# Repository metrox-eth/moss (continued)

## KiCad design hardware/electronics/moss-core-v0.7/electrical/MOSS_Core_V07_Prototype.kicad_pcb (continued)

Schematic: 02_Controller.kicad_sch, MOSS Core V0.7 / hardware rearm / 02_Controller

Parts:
C6: 10uF; Capacitor_SMD_C_0805_2012Metric; MPN GRM21BR71A106KA73L
C7, C41: 100nF; Capacitor_SMD_C_0603_1608Metric; MPN GRM188R71C104KA01D
D2: GREEN; LED_SMD_LED_0603_1608Metric; MPN LTST-C190KGKT
H1: M2.5 GND bond / drill2.7; MOSS_Mount_M2p5_GND_D8; MPN PCB_FEATURE
H2, H3, H4: M2.5 / drill 2.7 / keepout D8; MOSS_Mount_M2p5_2p7_D8; MPN NPTH
H5, H6, H7, H8: Orange Pi M2.5 / D6; MOSS_Mount_M2p5_2p7_D6; MPN NPTH
R5, R6: 10k; Resistor_SMD_R_0603_1608Metric; MPN RC0603FR-0710KL
R7: 1k; Resistor_SMD_R_0603_1608Metric; MPN RC0603FR-071KL
R8, R9: 4.7k; Resistor_SMD_R_0603_1608Metric; MPN RC0603FR-074K7L
SW1: RESET_N; Button_Switch_SMD_SW_Push_1P1T_NO_CK_KMR2; MPN KMR221NGLFS
SW2: BOOT_N; Button_Switch_SMD_SW_Push_1P1T_NO_CK_KMR2; MPN KMR221NGLFS
TP1: GND; TestPoint_TestPoint_Pad_D1.0mm; MPN PCB test pad
TP2: 3V3; TestPoint_TestPoint_Pad_D1.0mm; MPN PCB test pad
TP3: TX0; TestPoint_TestPoint_Pad_D1.0mm; MPN PCB test pad
TP5: SDA; TestPoint_TestPoint_Pad_D1.0mm; MPN PCB test pad
TP6: SCL; TestPoint_TestPoint_Pad_D1.0mm; MPN PCB test pad
TP7: RESET; TestPoint_TestPoint_Pad_D1.0mm; MPN PCB test pad
U1: ESP32-S3-WROOM-1U-N8; RF_Module_ESP32-S3-WROOM-1U; MPN ESP32-S3-WROOM-1U-N8
U20: TPS3808G33DBVR; Package_TO_SOT_SMD_SOT-23-6; MPN TPS3808G33DBVR

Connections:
3V3: C6.1, C7.1, C41.1, R5.1, R6.1, R8.1, R9.1, TP2.1, U1.2 (3V3), U20.5 (SENSE), U20.6 (VDD); also elsewhere on the board
ACT_POWER_ENABLE: U1.31 (IO38); also elsewhere on the board
ARM_COMMIT: U1.39 (IO1); also elsewhere on the board
ARM_LATCHED: U1.38 (IO2); also elsewhere on the board
AUDIO_BCLK: U1.18 (IO10); also elsewhere on the board
AUDIO_DATA: U1.20 (IO12); also elsewhere on the board
AUDIO_ENABLE: U1.21 (IO13); also elsewhere on the board
AUDIO_LRCLK: U1.19 (IO11); also elsewhere on the board
BOOT_N: R6.2, SW2.1 (A), U1.27 (IO0)
DEBUG_TX: TP3.1, U1.37 (IO43)
DIR_L: U1.10 (IO17); also elsewhere on the board
DIR_R: U1.12 (IO8); also elsewhere on the board
DRIVE_ENABLE: U1.23 (IO21); also elsewhere on the board
DRIVE_RUN: U1.36 (IO44); also elsewhere on the board
ENC_L_A: U1.7 (IO7); also elsewhere on the board
ENC_L_B: U1.6 (IO6); also elsewhere on the board
ENC_POWER_EN: U1.35 (IO42); also elsewhere on the board
ENC_R_A: U1.5 (IO5); also elsewhere on the board
ENC_R_B: U1.9 (IO16); also elsewhere on the board
ESP_USB_N: U1.13 (IO19); also elsewhere on the board
ESP_USB_P: U1.14 (IO20); also elsewhere on the board
ESTOP_ACTIVE: U1.4 (IO4); also elsewhere on the board
GND: C6.2, C7.2, C41.2, D2.1 (K), H1.1 (GND), SW1.2 (B), SW2.2 (B), TP1.1, U1.1 (GND), U1.40 (GND), U1.41 (GND), U20.2 (GND); also elsewhere on the board
I2C_SCL: R9.2, TP6.1, U1.33 (IO40); also elsewhere on the board
I2C_SDA: R8.2, TP5.1, U1.34 (IO41); also elsewhere on the board
LED_A: D2.2 (A), R7.2
PWM_L: U1.11 (IO18); also elsewhere on the board
PWM_R: U1.17 (IO9); also elsewhere on the board
RESET_N: R5.2, SW1.1 (A), TP7.1, U1.3 (EN), U20.1 (RESET_N); also elsewhere on the board
SERVO_RX: U1.30 (IO37); also elsewhere on the board
SERVO_TX: U1.28 (IO35); also elsewhere on the board
SERVO_TX_ENABLE: U1.29 (IO36); also elsewhere on the board
STATUS_LED: R7.1, U1.8 (IO15)
USB_PWR_FAULT_N: U1.22 (IO14); also elsewhere on the board
WD_ENABLE: U1.24 (IO47); also elsewhere on the board
WD_RESET_N: U20.3 (MR_N); also elsewhere on the board
WD_TICK: U1.25 (IO48); also elsewhere on the board

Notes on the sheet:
MOSS CORE V0.7 / ASYNC FAULT CLEAR + EXPLICIT REARM / 1 NOVEMBER 2026
GPIO1 ARM_COMMIT is a dedicated post-qualification pulse. GPIO2 reads ARM_LATCHED. Initial ACT_POWER_ENABLE remains independent of ACT_READY.

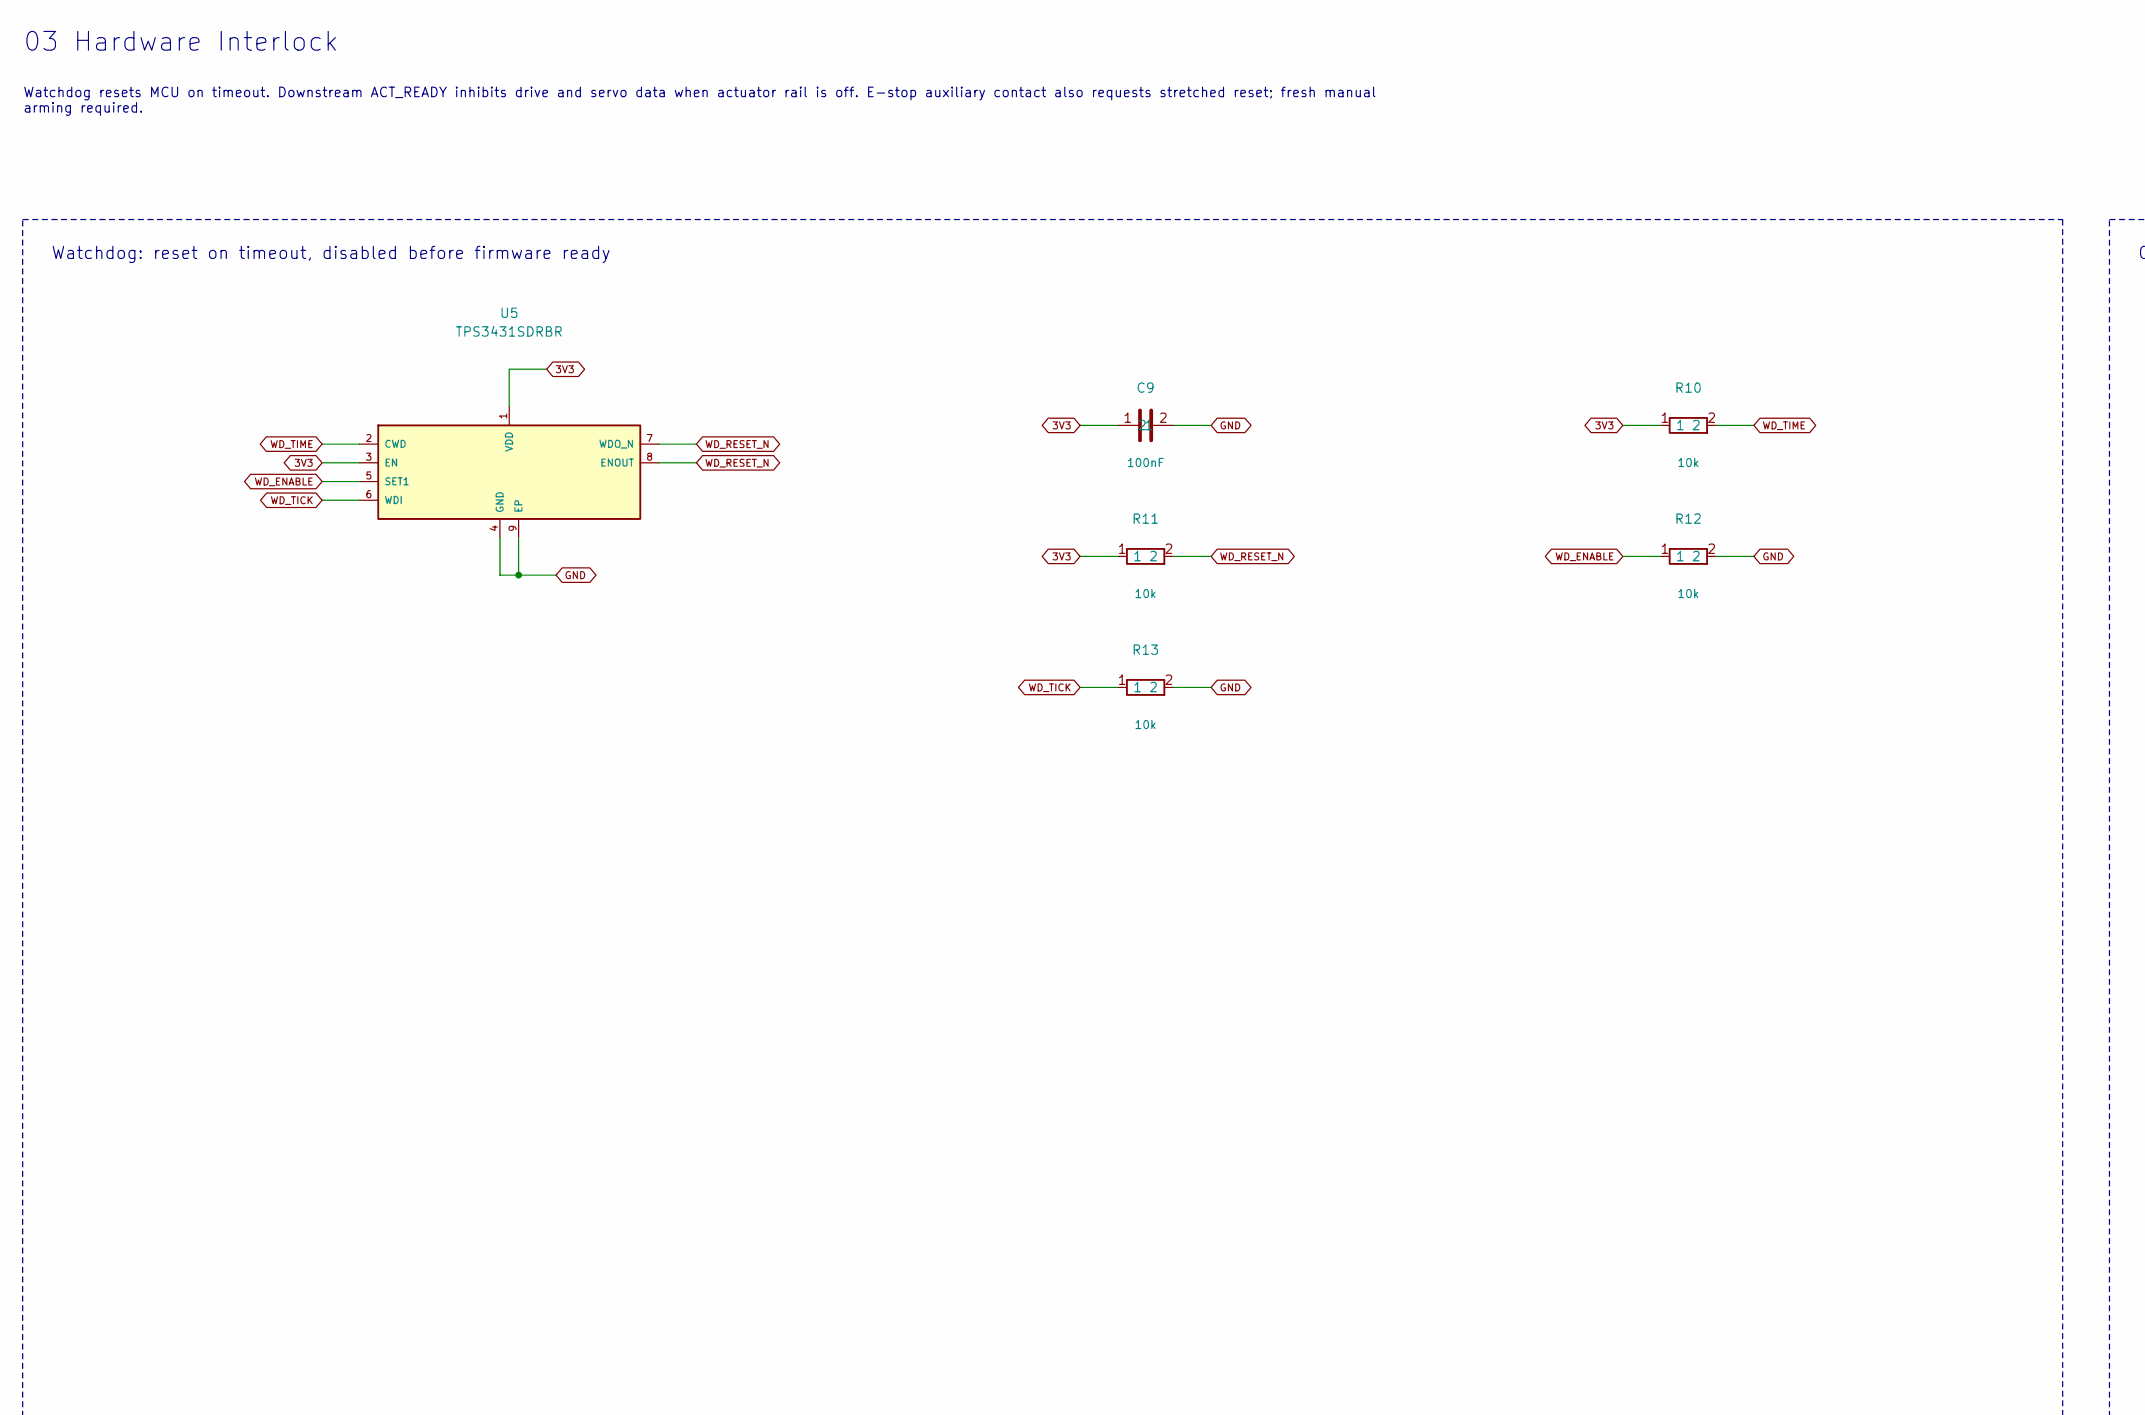
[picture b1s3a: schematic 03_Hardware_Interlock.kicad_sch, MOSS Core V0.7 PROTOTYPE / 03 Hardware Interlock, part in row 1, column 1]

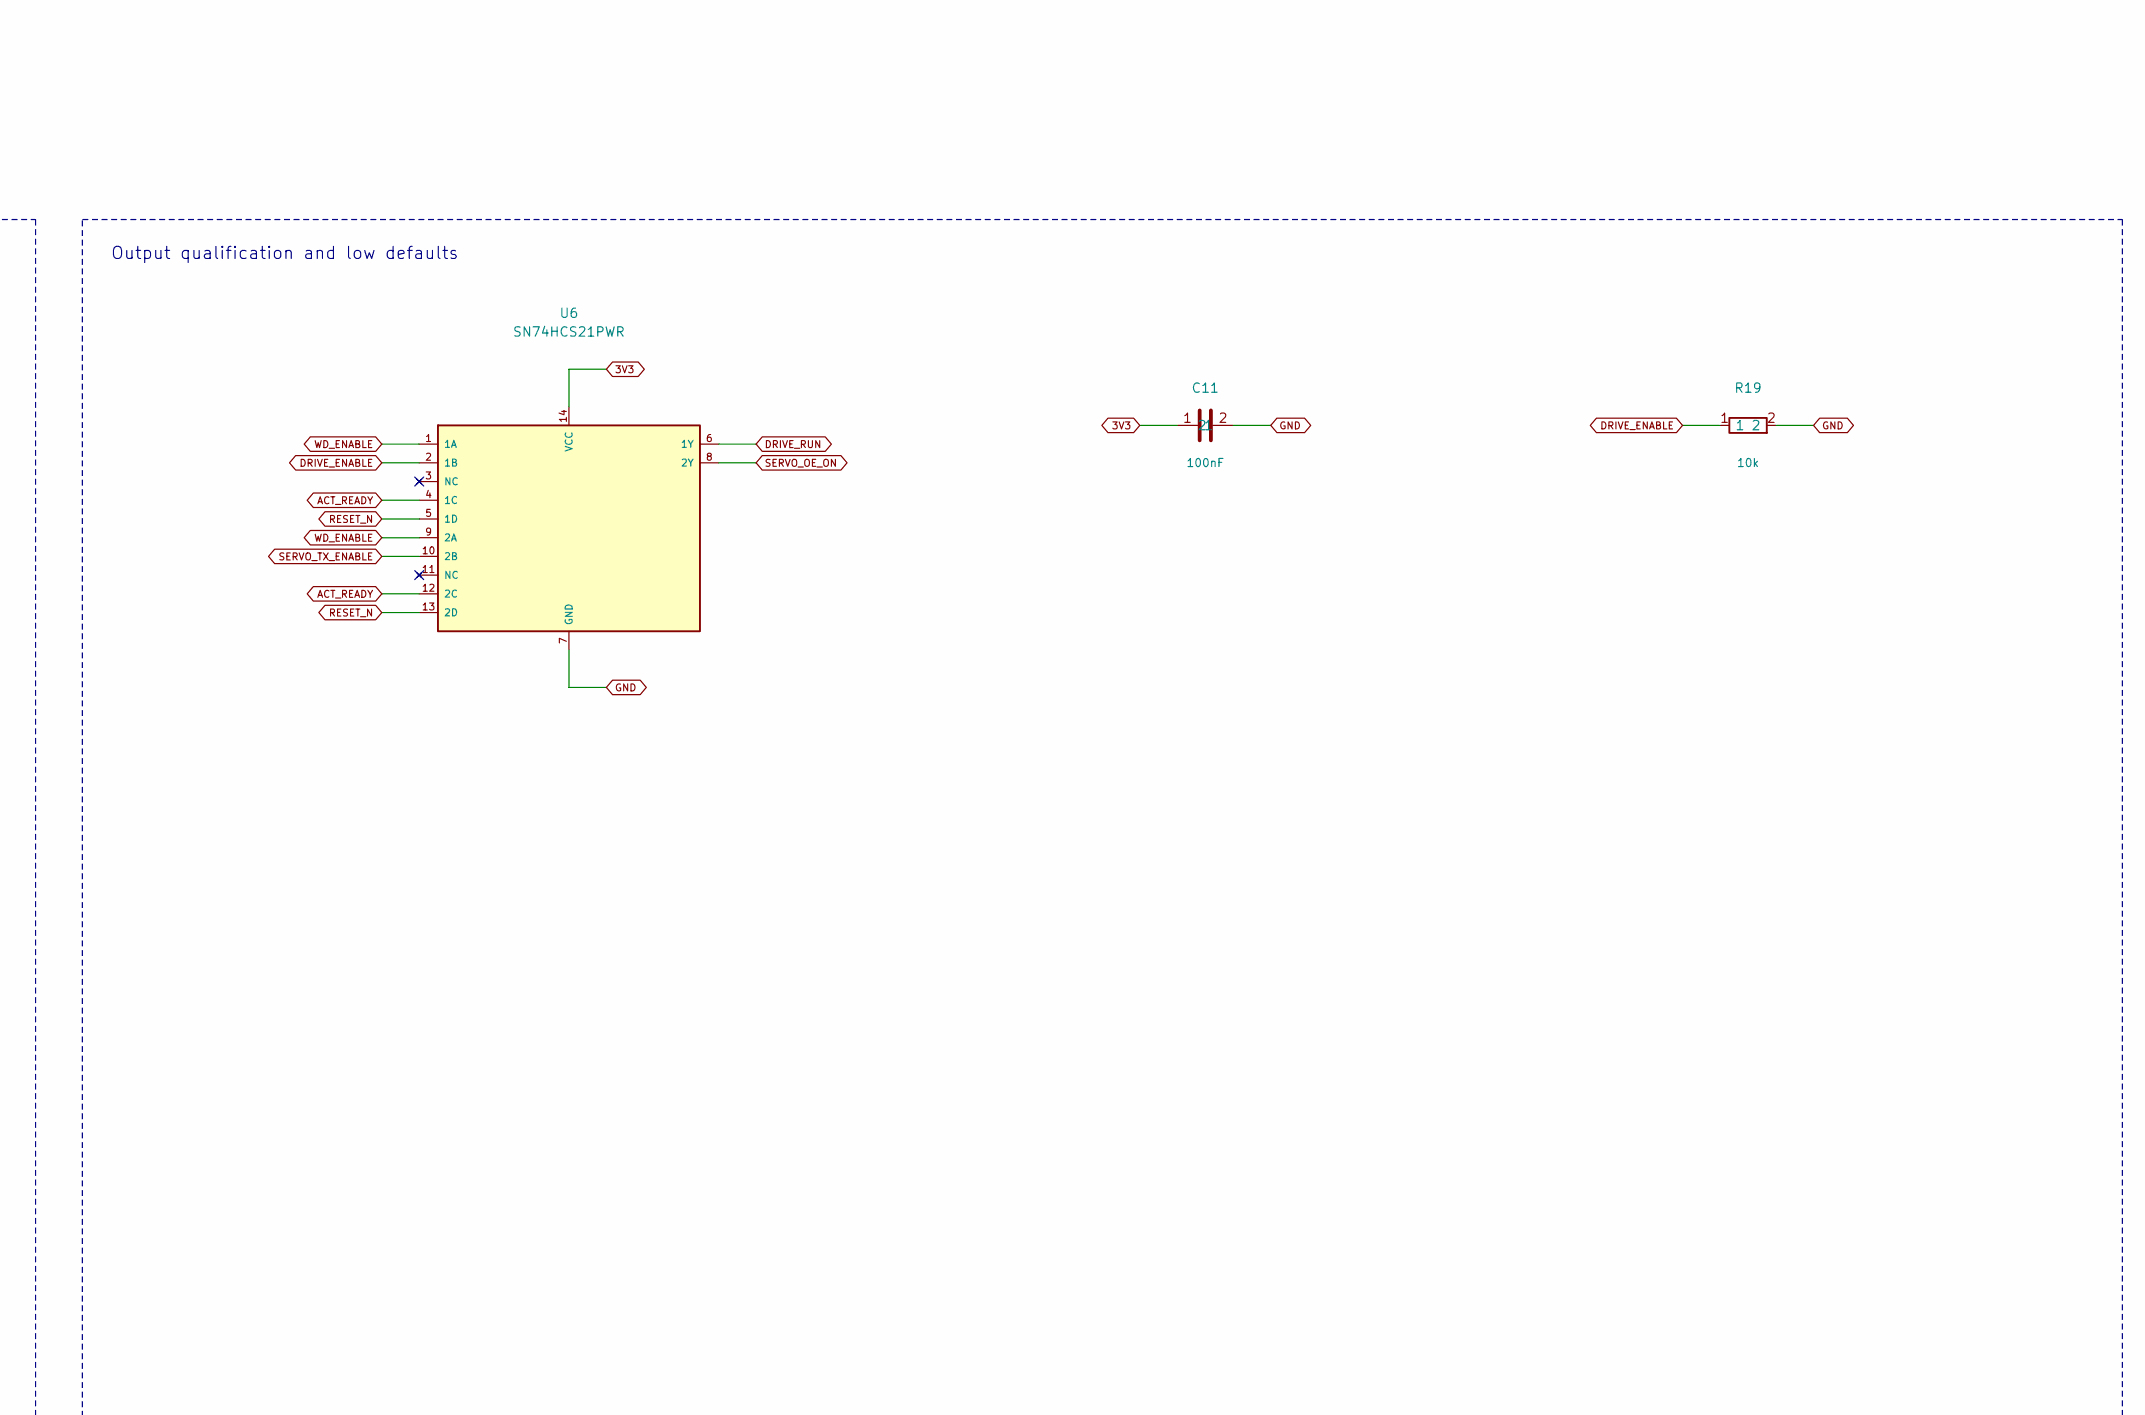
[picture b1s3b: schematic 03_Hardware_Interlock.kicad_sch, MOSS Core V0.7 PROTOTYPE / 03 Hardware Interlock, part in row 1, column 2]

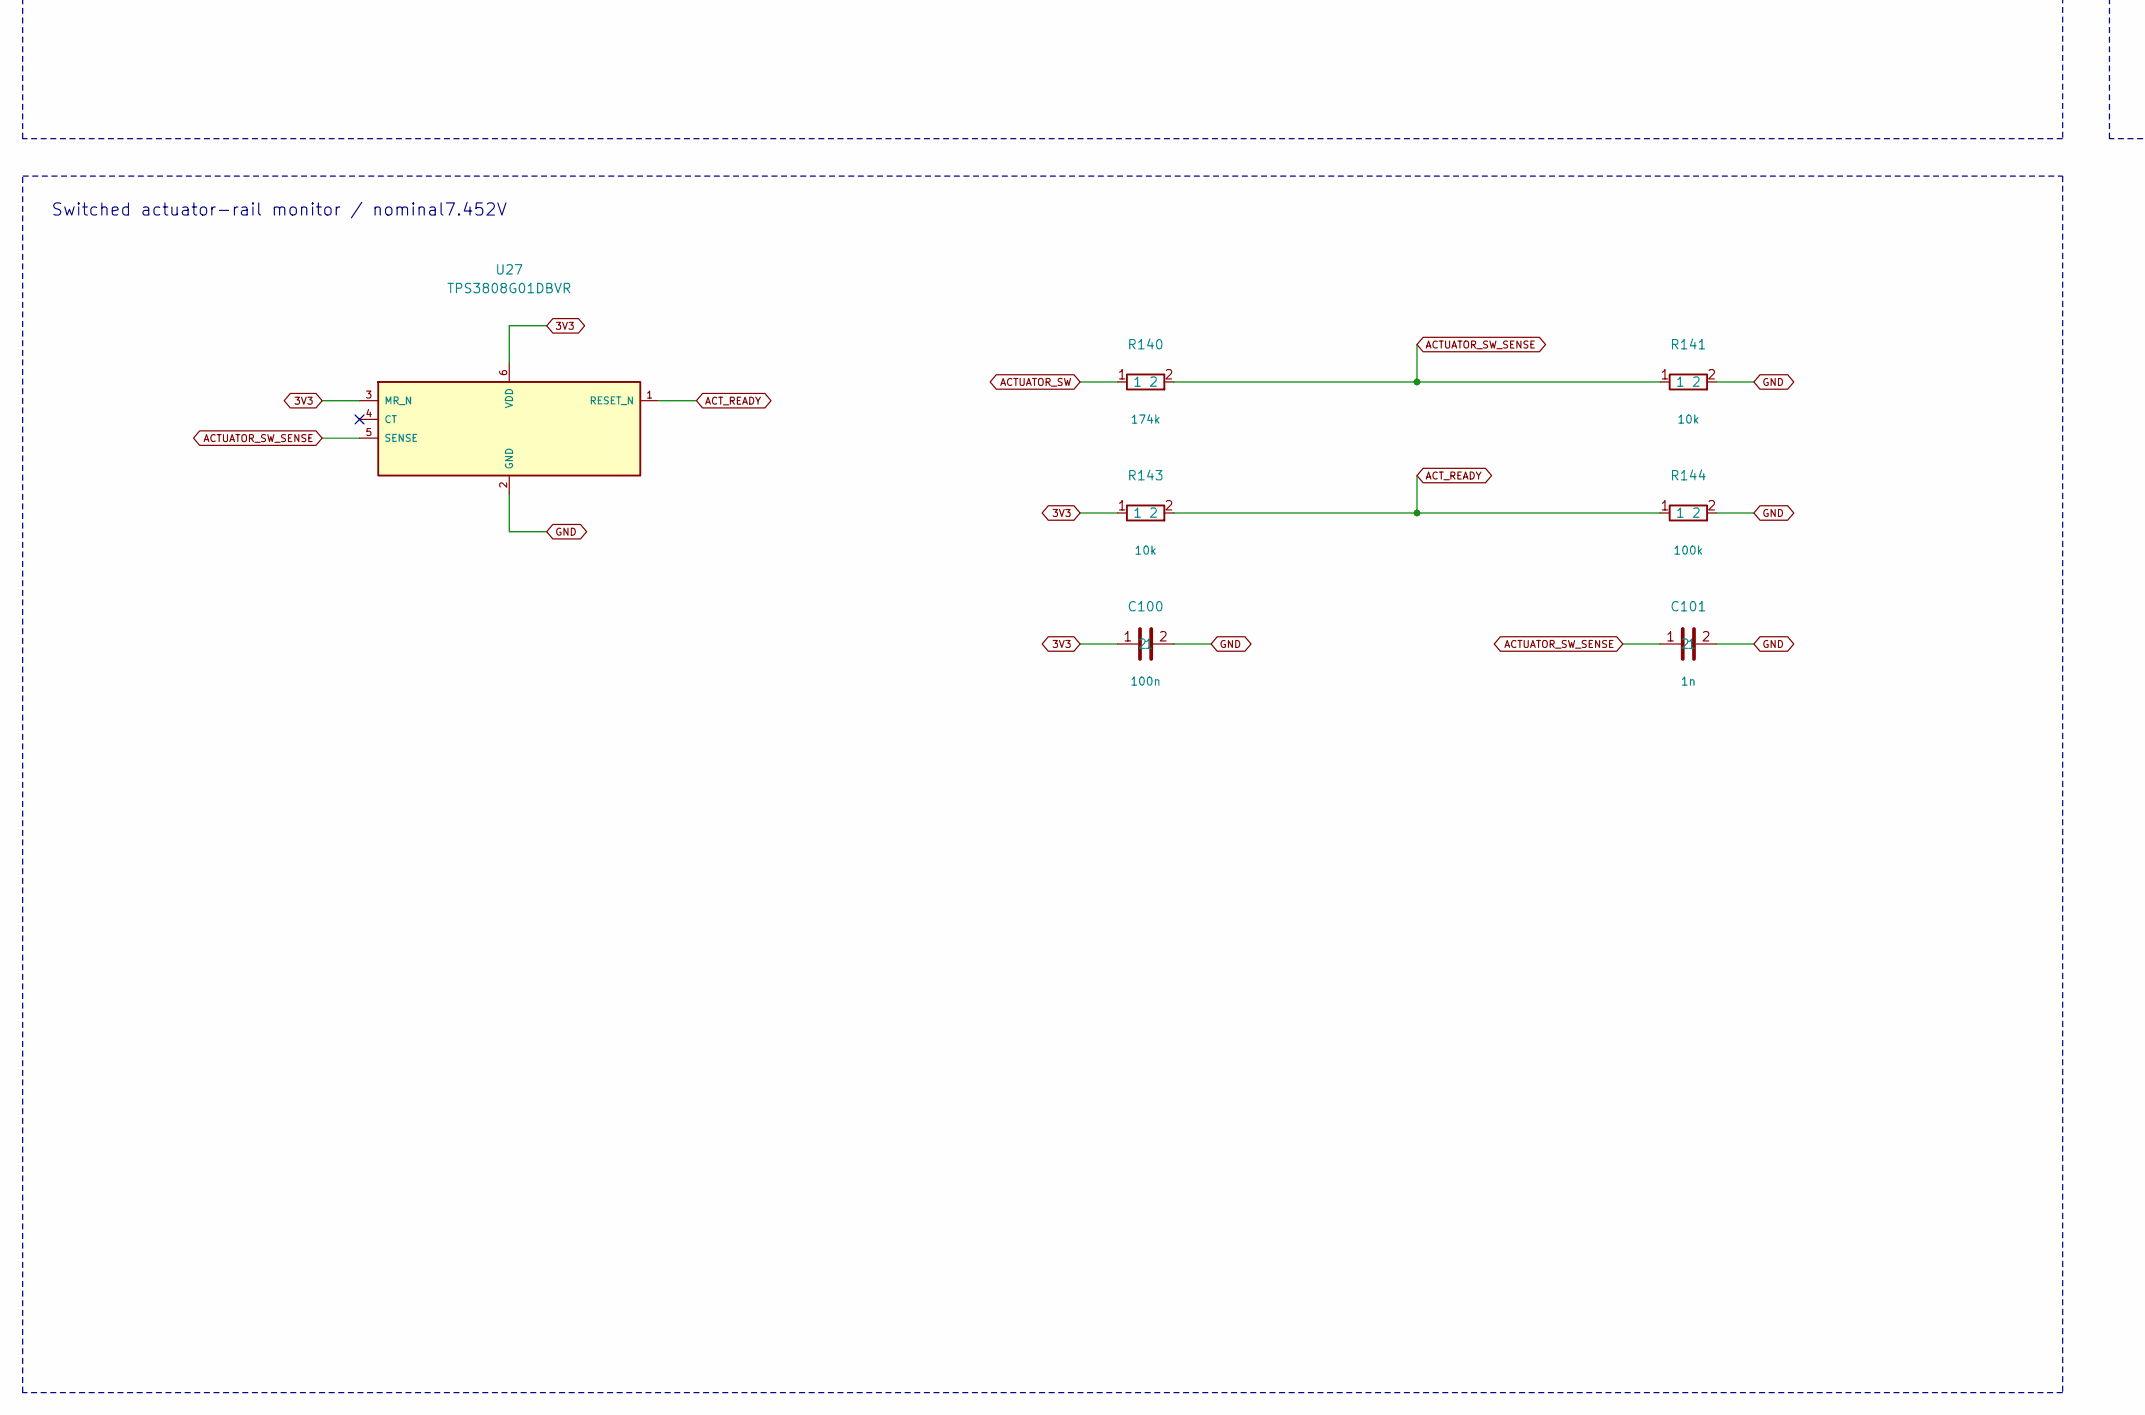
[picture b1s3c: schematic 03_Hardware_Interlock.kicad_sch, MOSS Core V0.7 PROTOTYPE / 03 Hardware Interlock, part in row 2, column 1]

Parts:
C9, C11: 100nF; Capacitor_SMD_C_0603_1608Metric; MPN GRM188R71C104KA01D
C100: 100n; Capacitor_SMD_C_0603_1608Metric; MPN GRM188R71C104KA01D
C101: 1n; Capacitor_SMD_C_0603_1608Metric; MPN GRM1885C1H102JA01D
R10, R11, R12, R13, R19, R143: 10k; Resistor_SMD_R_0603_1608Metric; MPN RC0603FR-0710KL
R140: 174k; Resistor_SMD_R_0603_1608Metric; MPN RT0603BRD07174KL
R141: 10k; Resistor_SMD_R_0603_1608Metric; MPN RT0603BRD0710KL
R144: 100k; Resistor_SMD_R_0603_1608Metric; MPN RC0603FR-07100KL
U5: TPS3431SDRBR; Package_SON_VSON-8-1EP_3x3mm_P0.65mm_EP1.65x2.4mm; MPN TPS3431SDRBR
U6: SN74HCS21PWR; Package_SO_TSSOP-14_4.4x5mm_P0.65mm; MPN SN74HCS21PWR
U27: TPS3808G01DBVR; Package_TO_SOT_SMD_SOT-23-6; MPN TPS3808G01DBVR

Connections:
3V3: C9.1, C11.1, C100.1, R10.1, R11.1, R143.1, U5.1 (VDD), U5.3 (EN), U6.14 (VCC), U27.3 (MR_N), U27.6 (VDD); also elsewhere on the board
ACTUATOR_SW: R140.1; also elsewhere on the board
ACTUATOR_SW_SENSE: C101.1, R140.2, R141.1, U27.5 (SENSE)
DRIVE_ENABLE: R19.1, U6.2 (1B); also elsewhere on the board
DRIVE_RUN: U6.6 (1Y); also elsewhere on the board
GND: C9.2, C11.2, C100.2, C101.2, R12.2, R13.2, R19.2, R141.2, R144.2, U5.4 (GND), U5.9 (EP), U6.7 (GND), U27.2 (GND); also elsewhere on the board
RESET_N: U6.5 (1D), U6.13 (2D); also elsewhere on the board
SERVO_OE_ON: U6.8 (2Y); also elsewhere on the board
SERVO_TX_ENABLE: U6.10 (2B); also elsewhere on the board
WD_ENABLE: R12.1, U5.5 (SET1), U6.1 (1A), U6.9 (2A); also elsewhere on the board
WD_RESET_N: R11.2, U5.7 (WDO_N), U5.8 (ENOUT); also elsewhere on the board
WD_TICK: R13.1, U5.6 (WDI); also elsewhere on the board
WD_TIME: R10.2, U5.2 (CWD)

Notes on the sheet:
03 Hardware Interlock
Watchdog resets MCU on timeout. Downstream ACT_READY inhibits drive and servo data when actuator rail is off. E-stop auxiliary contact also requests stretched reset; fresh manual arming required.
Watchdog: reset on timeout, disabled before firmware ready
Output qualification and low defaults
Switched actuator-rail monitor / nominal7.452V

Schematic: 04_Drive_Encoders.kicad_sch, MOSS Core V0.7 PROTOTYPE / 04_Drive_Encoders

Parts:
C18, C23: 100nF; Capacitor_SMD_C_0603_1608Metric; MPN GRM188R71C104KA01D
C19, C20, C21, C22: 100pF; Capacitor_SMD_C_0603_1608Metric; MPN GRM1885C1H101JA01D
C43, C44: 1uF; Capacitor_SMD_C_0603_1608Metric; MPN GRM188R61A105KA61D
C45: 10nF; Capacitor_SMD_C_0603_1608Metric; MPN GRM188R71H103KA01D
D6, D7, D8, D9: PESD5V0S1BA; Diode_SMD_D_SOD-323; MPN PESD5V0S1BA,115
J2: CYTRON LINK; Connector_Molex_Molex_Micro-Fit_3.0_43045-1012_2x05_P3.00mm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; MPN 43045-1012
J3: LEFT MOTOR + ENCODER; Connector_Molex_Molex_Micro-Fit_3.0_43045-0612_2x03_P3.00mm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; MPN 43045-0612
J4: RIGHT MOTOR + ENCODER; Connector_Molex_Molex_Micro-Fit_3.0_43045-0612_2x03_P3.00mm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; MPN 43045-0612
R23, R25, R27, R29: 100; Resistor_SMD_R_0603_1608Metric; MPN RC0603FR-07100RL
R24, R26, R28, R30, R36, R38, R40, R42: 10k; Resistor_SMD_R_0603_1608Metric; MPN RC0603FR-0710KL
R31, R32, R33, R34, R75: 47k; Resistor_SMD_R_0603_1608Metric; MPN RC0603FR-0747KL
R35, R37, R39, R41: 1k; Resistor_SMD_R_0603_1608Metric; MPN RC0603FR-071KL
R76, R77, R78, R79: 100k; Resistor_SMD_R_0603_1608Metric; MPN RC0603FR-07100KL
U11: 74LV08APWJ; Package_SO_TSSOP-14_4.4x5mm_P0.65mm; MPN 74LV08APWJ
U12: SN74LVC14APWR; Package_SO_TSSOP-14_4.4x5mm_P0.65mm; MPN SN74LVC14APWR
U22: TPS22918DBVR; Package_TO_SOT_SMD_SOT-23-6; MPN TPS22918DBVR

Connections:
3V3: C18.1, C23.1, C43.1, U11.14 (VCC), U12.14 (VCC), U22.1 (VIN); also elsewhere on the board
CYTRON_L_LEAD: J2.6 (LEFT_A); also elsewhere on the board
CYTRON_R_LEAD: J2.8 (RIGHT_A); also elsewhere on the board
DIR_L: R33.1, U11.9 (3A); also elsewhere on the board
DIR_L_SAFE: R25.1, U11.8 (3Y)
DIR_R: R34.1, U11.12 (4A); also elsewhere on the board
DIR_R_SAFE: R29.1, U11.11 (4Y)
DRIVE_RUN: U11.2 (1B), U11.5 (2B), U11.10 (3B), U11.13 (4B); also elsewhere on the board
EL_A_EXT: D6.1, J3.5 (ENC_A), R35.1
EL_A_F: C19.1, R35.2, R36.2, R76.1, U12.1 (1A)
EL_B_EXT: D7.1, J3.6 (ENC_B), R37.1
EL_B_F: C20.1, R37.2, R38.2, R77.1, U12.3 (2A)
ENC_3V3: C44.1, J3.4 (ENC_3V3), J4.4 (ENC_3V3), R36.1, R38.1, R40.1, R42.1, U22.5 (QOD), U22.6 (VOUT)
ENC_L_A: U12.2 (1Y); also elsewhere on the board
ENC_L_B: U12.4 (2Y); also elsewhere on the board
ENC_POWER_EN: R75.1, U22.3 (ON); also elsewhere on the board
ENC_R_A: U12.6 (3Y); also elsewhere on the board
ENC_R_B: U12.8 (4Y); also elsewhere on the board
ENC_SLEW_CT: C45.1, U22.4 (CT)
ER_A_EXT: D8.1, J4.5 (ENC_A), R39.1
ER_A_F: C21.1, R39.2, R40.2, R78.1, U12.5 (3A)
ER_B_EXT: D9.1, J4.6 (ENC_B), R41.1
ER_B_F: C22.1, R41.2, R42.2, R79.1, U12.9 (4A)
GND: C18.2, C19.2, C20.2, C21.2, C22.2, C23.2, C43.2, C44.2, C45.2, D6.2, D7.2, D8.2, D9.2, J2.5 (SIGNAL_GND), J3.3 (ENC_GND), J4.3 (ENC_GND), R24.2, R26.2, R28.2, R30.2, R31.2, R32.2, R33.2, R34.2, R75.2, R76.2, R77.2, R78.2, R79.2, U11.7 (GND), U12.7 (GND), U12.11 (5A), U12.13 (6A), U22.2 (GND); also elsewhere on the board
MDD_DIR1: J2.2 (DIR1), R25.2, R26.1
MDD_DIR2: J2.4 (DIR2), R29.2, R30.1
MDD_PWM1: J2.1 (PWM1), R23.2, R24.1
MDD_PWM2: J2.3 (PWM2), R27.2, R28.1
MOTOR_L_LEAD: J3.1 (M1); also elsewhere on the board
MOTOR_L_RETURN: J2.7 (LEFT_B), J3.2 (M2)
MOTOR_R_LEAD: J4.1 (M1); also elsewhere on the board
MOTOR_R_RETURN: J2.9 (RIGHT_B), J4.2 (M2)
PWM_L: R31.1, U11.1 (1A); also elsewhere on the board
PWM_L_SAFE: R23.1, U11.3 (1Y)
PWM_R: R32.1, U11.4 (2A); also elsewhere on the board
PWM_R_SAFE: R27.1, U11.6 (2Y)

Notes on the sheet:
MOSS CORE V0.7 / SIMPLIFIED MOTOR HARNESS / 31 OCTOBER 2026
One six-wire cable per motor. J2 to Cytron: four bridge outputs + PWM/DIR controls. Supply separately on J11.
